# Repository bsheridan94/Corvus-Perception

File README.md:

# Corvus-Perception
IoT Data Fusion Engine for
Interior Home Application

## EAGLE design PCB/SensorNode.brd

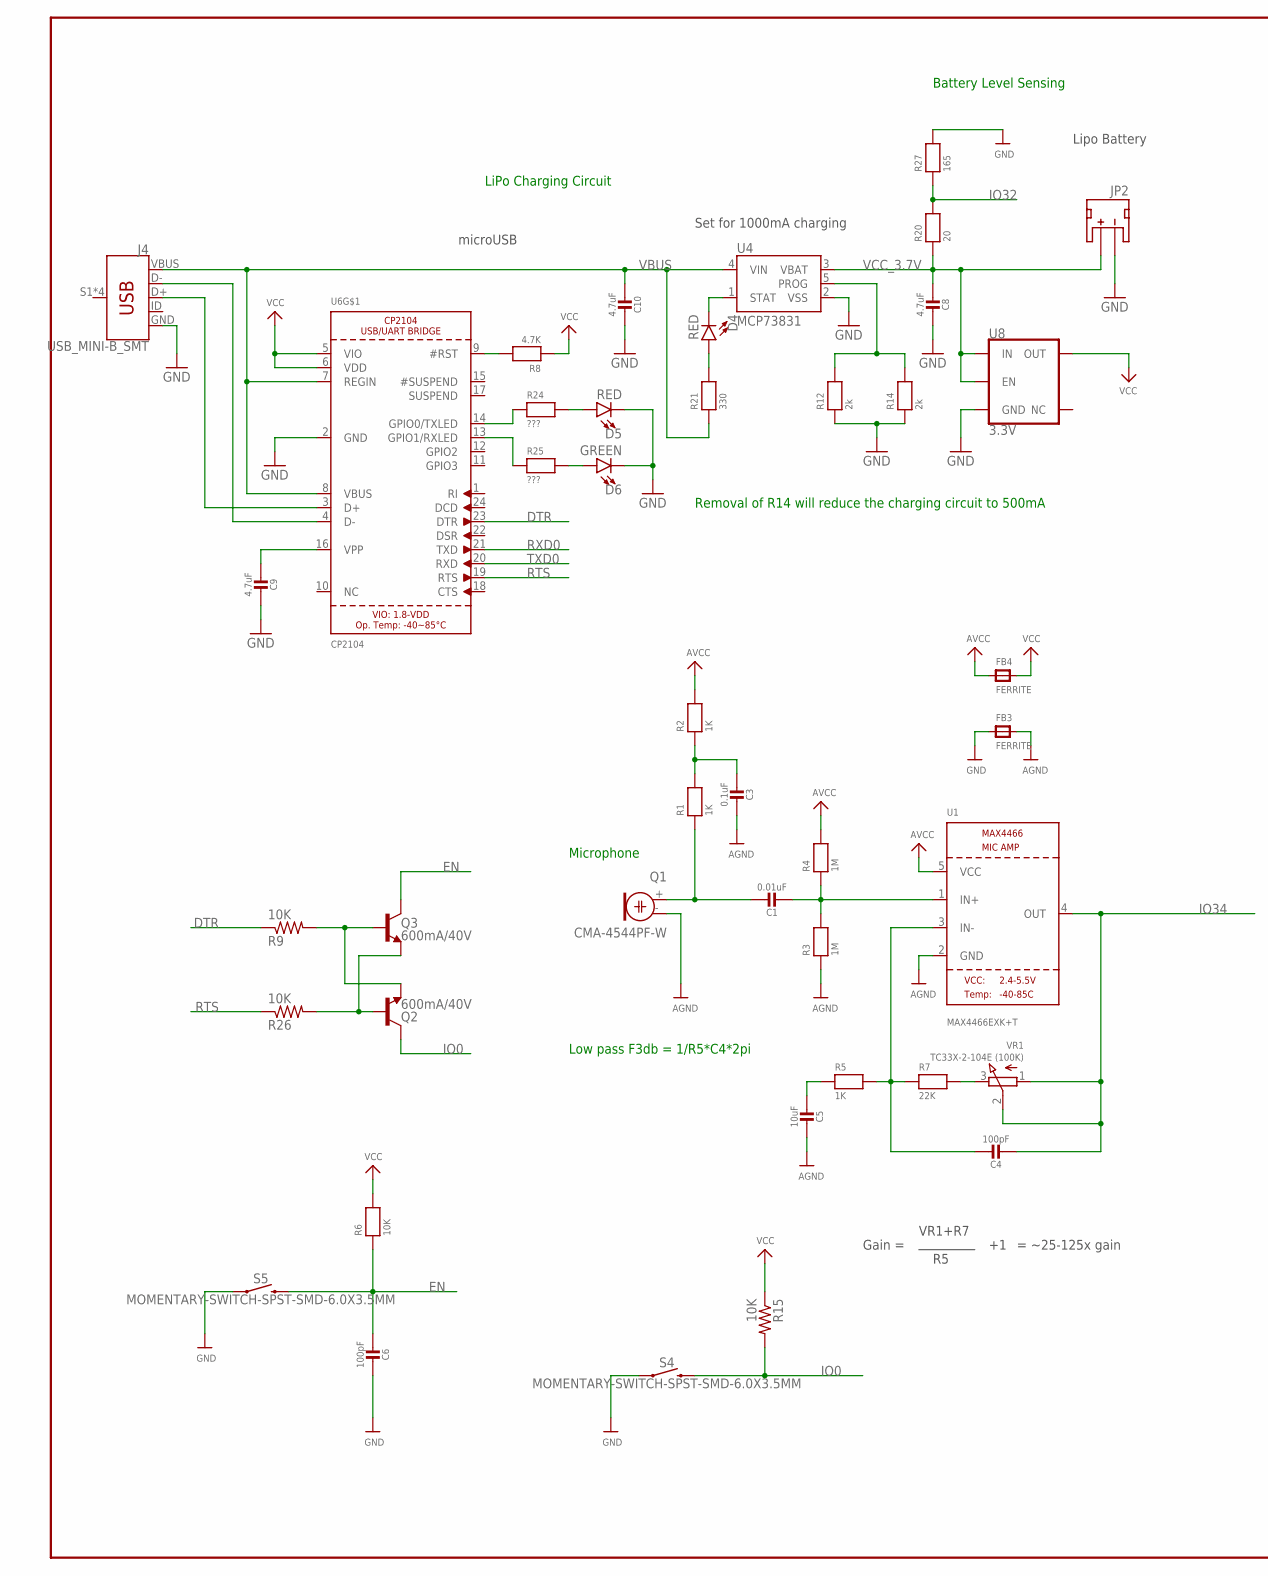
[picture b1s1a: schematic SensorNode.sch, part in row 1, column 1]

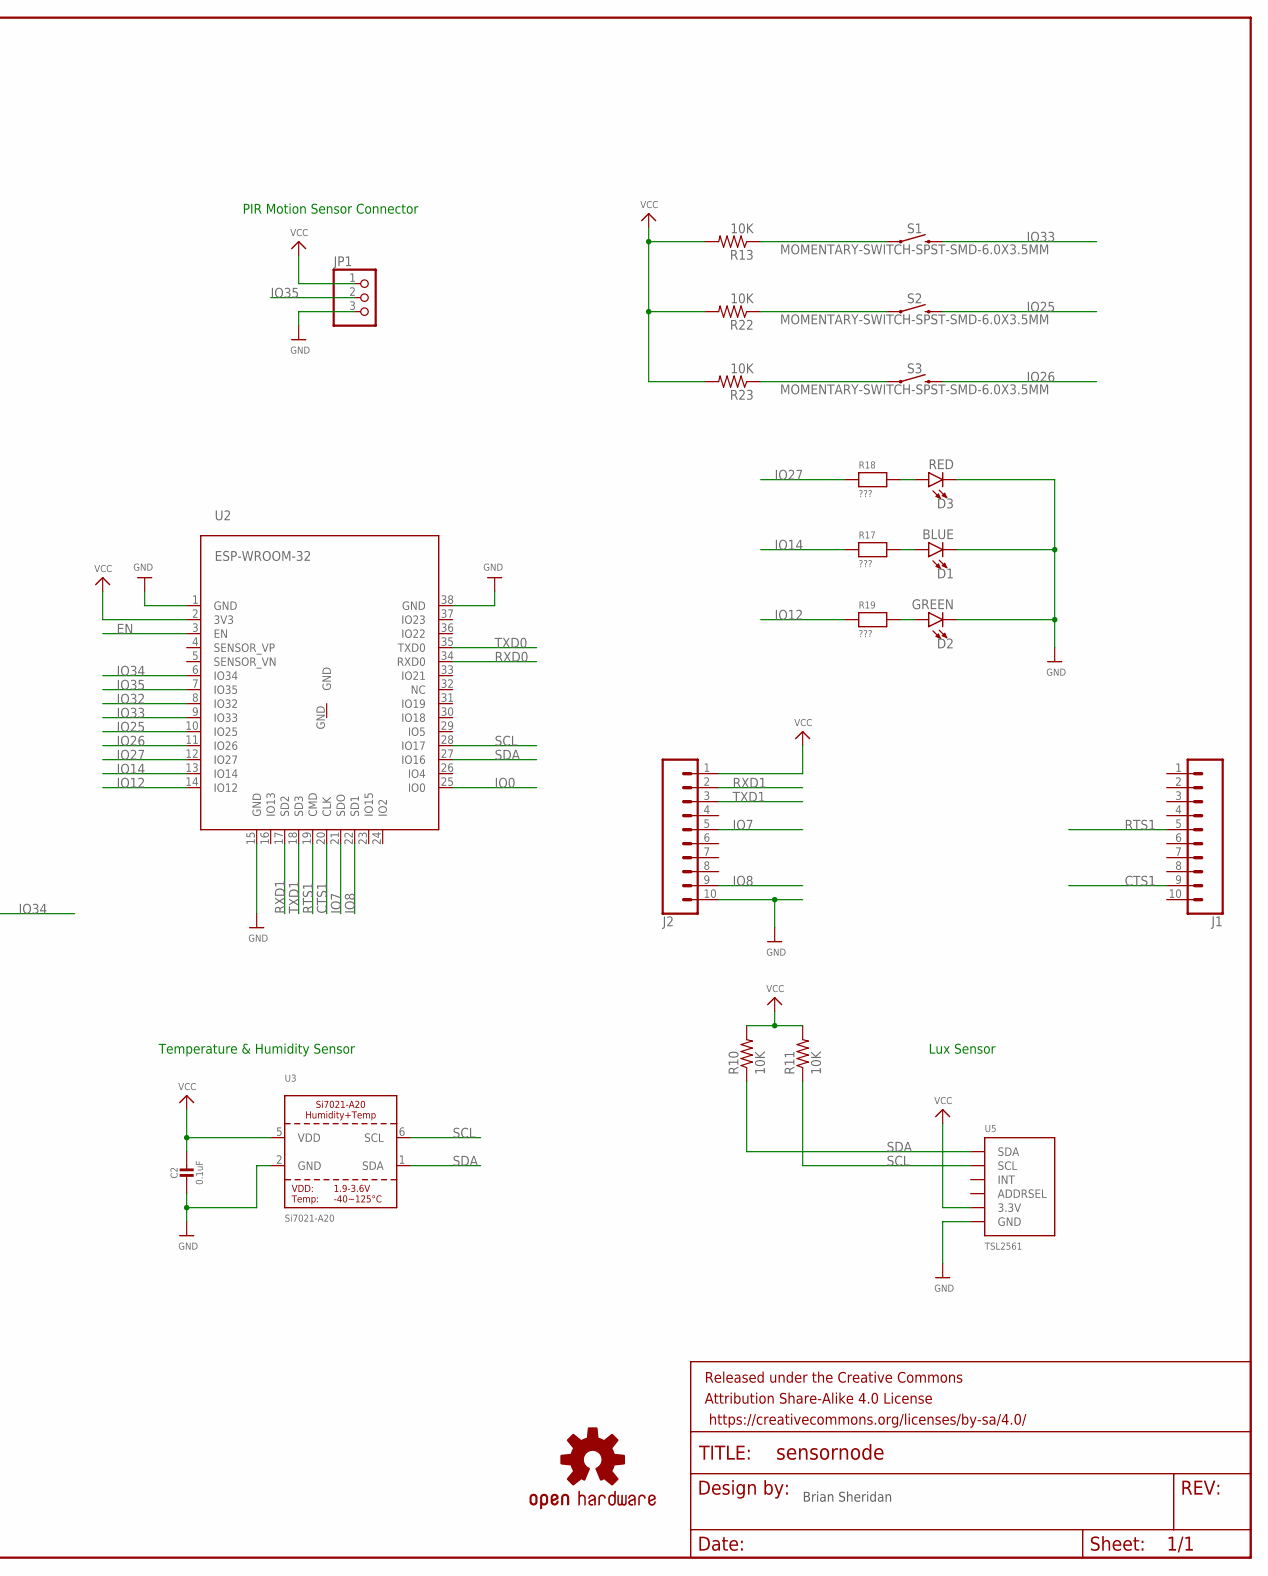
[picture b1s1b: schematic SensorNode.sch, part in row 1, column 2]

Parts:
C1: 0.01uF; 0805-NO
C2, C3: 0.1uF; 0805-NO
C4, C6: 100pF; 0805-NO
C5: 10uF; 0805-NO
C8, C9, C10: 4.7uF; 0805-NO
D1: BLUE; LED-1206
D2, D6: GREEN; LED-1206
D3, D4, D5: RED; LED-1206
FB3, FB4: FERRITE; 0805
FRAME1: FRAME-LEDGER; CREATIVE_COMMONS
J1, J2: CONN_102MMSMD; 1X10-2MM-SMD
J4: USB_MINI-B_SMT; USB-MINIB
JP1: HEADER-1X376MIL; 1X03_ROUND_76
JP2: JST; JST-2-SMD
LOGO1: OSHW-LOGOM; OSHW-LOGO-M
Q1: CMA-4544PF-W; ELECTRET_9.7
Q2, Q3: 600mA/40V; SOT23-3
R1, R2, R5: 1K; 0805
R3, R4: 1M; 0805
R6: 10K; 0805
R7: 22K; 0805
R8: 4.7K; 0805
R9, R10, R11, R13, R15, R22, R23, R26: 10K; R0805
R12, R14: 2k; 0805
R17, R18, R19, R24, R25: ???; 0805
R20: 20; 0805
R21: 330; 0805
R27: 165; 0805
S1, S2, S3, S4, S5: MOMENTARY-SWITCH-SPST-SMD-6.0X3.5MM; TACTILE_SWITCH_SMD_6.0X3.5MM
U1: MAX4466EXK+T; SC70-5
U2: ESP-WROOM-32
U3: Si7021-A20; DFN6_3X3_SI
U4: MCP73831; SOT23-5
U5: TSL2561; TSL2561_FN
U6: CP2104; QFN24_4MM_SMSC
U8: 3.3V; SOT23-5
VR1: TC33X-2-104E (100K); TRIMPOT_BOURNS_TC33X-2

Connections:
AGND: C3.1, C5.1, FB3.2, Q1.- (1), R3.1, U1.2 (GND)
AVCC: FB4.1, R2.2, R4.2, U1.5 (VCC)
CTS1: J1.9, U2.20 (CLK)
DTR: R9.1, U6.23 (DTR)
EN: C6.2, Q3.3 (C), R6.1, S5.2, U2.3 (EN)
GND: C2.2, C6.1, C8.1, C9.1, C10.1, D1.C, D2.C, D3.C, D5.C, D6.C, FB3.1, J2.10, J4.GND, JP1.3, JP2.1 (-), R12.1, R14.1, R27.2, S4.1, S5.1, U2.1 (GND), U2.15 (GND), U2.38 (GND), U3.2 (GND), U4.2 (VSS), U5.VSS (GND), U6.2 (GND), U8.2 (GND)
IO0: Q2.3 (C), R15.2, S4.2, U2.25 (IO0)
IO7: J2.5, U2.21 (SDO)
IO8: J2.9, U2.22 (SD1)
IO12: R19.1, U2.14 (IO12)
IO14: R17.1, U2.13 (IO14)
IO25: S2.2, U2.10 (IO25)
IO26: S3.2, U2.11 (IO26)
IO27: R18.1, U2.12 (IO27)
IO32: R20.2, R27.1, U2.8 (IO32)
IO33: S1.2, U2.9 (IO33)
IO34: C4.2, U1.4 (OUT), U2.6 (IO34), VR1.1 (A), VR1.2 (S)
IO35: JP1.2, U2.7 (IO35)
unnamed: C1.1, Q1.+ (2), R1.1
unnamed: C1.2, R3.2, R4.1, U1.1 (IN+)
unnamed: C4.1, R5.2, R7.1, U1.3 (IN-)
unnamed: C5.2, R5.1
unnamed: R7.2, VR1.3 (E)
unnamed: C9.2, U6.16 (VPP)
unnamed: R8.2, U6.9 (#RST)
unnamed: Q2.2 (E), Q3.1 (B), R9.2
unnamed: Q2.1 (B), Q3.2 (E), R26.2
unnamed: D4.A, R21.2
unnamed: R13.1, S1.1
unnamed: D3.A, R18.2
unnamed: D1.A, R17.2
unnamed: D2.A, R19.2
unnamed: R22.1, S2.1
unnamed: R23.1, S3.1
unnamed: C3.2, R1.2, R2.1
unnamed: J4.D-, U6.4 (D-)
unnamed: J4.D+, U6.3 (D+)
unnamed: D5.A, R24.2
unnamed: R24.1, U6.14 (GPIO0/TXLED)
unnamed: R25.1, U6.13 (GPIO1/RXLED)
unnamed: D6.A, R25.2
PROG: R12.2, R14.2, U4.5 (PROG)
RTS: R26.1, U6.19 (RTS)
RTS1: J1.5, U2.19 (CMD)
RXD0: U2.34 (RXD0), U6.21 (TXD)
RXD1: J2.2, U2.17 (SD2)
SCL: R11.1, U2.28 (IO17), U3.6 (SCL), U5.CLK (SCL)
SDA: R10.1, U2.27 (IO16), U3.1 (SDA), U5.DATA (SDA)
STAT: D4.C, U4.1 (STAT)
TP: U6.THERM (TP)
TXD0: U2.35 (TXD0), U6.20 (RXD)
TXD1: J2.3, U2.18 (SD3)
VBUS: C10.2, J4.VBUS, R21.1, U4.4 (VIN), U6.7 (REGIN), U6.8 (VBUS)
VCC: C2.1, FB4.2, J2.1, JP1.1, R6.2, R8.1, R10.2, R11.2, R13.2, R15.1, R22.2, R23.2, U2.2 (3V3), U3.5 (VDD), U5.VDD (3.3V), U6.5 (VIO), U6.6 (VDD), U8.5 (OUT)
VCC_3.7V: C8.2, JP2.2 (+), R20.1, U4.3 (VBAT), U8.1 (IN), U8.3 (EN)

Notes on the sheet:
Gain =
VR1+R7
= ~25-125x gain
Low pass F3db = 1/R5*C4*2pi
PIR Motion Sensor Connector
Set for 1000mA charging
microUSB
Lipo Battery
LiPo Charging Circuit
Microphone
Temperature & Humidity Sensor
Lux Sensor
Battery Level Sensing
Removal of R14 will reduce the charging circuit to 500mA
Brian Sheridan

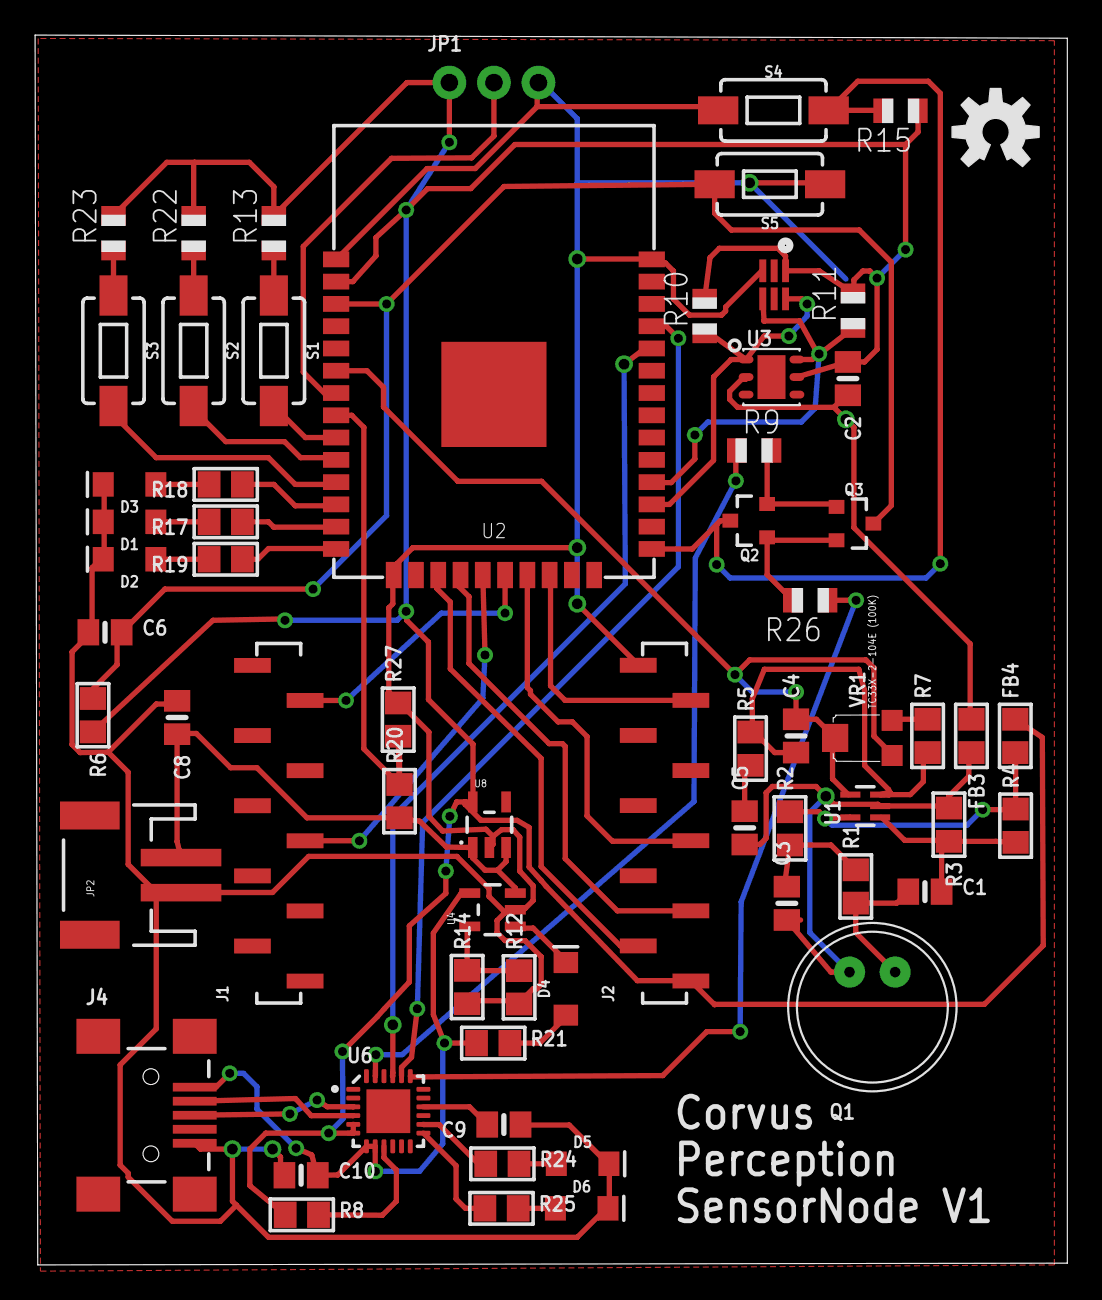
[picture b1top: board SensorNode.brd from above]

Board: 2 copper layers, 58.9 x 70.1 mm, 66 parts (0 on the bottom side), 54 nets.

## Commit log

2017-02-05 :tada: Added .gitattributes & .gitignore files
2017-02-05 Inital Commit. Migration from STM32F4 to ESP32
2017-02-05 Added hardware Documentation
2017-02-07 PCB Improvements, layout planned out
    Moved components around on layout to minimize pcb space. Battery moved
    to back of board. Minor schematic improvements. ESP32 template added
2017-02-08 Added USB to UART and Auto Reset Circuit
2017-02-23 Reset and Bootloader PushButtons, Replaced USB
    USB micro to mini due to supply issues.
    SMD Xbee headers
    New voltage regulator
2017-02-26 Created Android Wear App
    Sets the smart watch's bluetooth to discoverable.
2017-02-27 Add files via upload
    Website Template
2017-02-28 Fixed Net Issues, Started Routing
2017-03-01 Mid Route Check Point
2017-03-02 Commit Before AutoRouting
2017-03-02 Fully Routed
2017-03-02 Added system health icon
2017-03-10 Post DRC layout
2017-03-11 Added demo script and template updates
    Fixed acknowledgement button
    Added slider to webpage (not active)
    Added demo php file
2017-03-12 Rewrote Awknowledgement Button
    Added working acknowledgement for each alert
    Connected MySQL database to web front end
2017-03-13 Temperature Alert Working
    Added "test/debug" panel
    Fixed Acknowledgement button to be more accurate
    Added temperature test case
2017-05-03 Added Working Sensitivity Functions
2017-05-06 testing ts12561
2017-05-13 Working TSL2561 Driver
2017-05-22 Added Alexa Support
2017-05-22 fall detection
2017-05-22 fall
2017-05-25 Fall Alert
    Python code for Pi when user falls
2017-05-25 Updated to remove logger error
2017-05-25 Added dynamic temperature Alert
2017-05-25 Pi to AWS RDS script
    Once the packet is parsed, this adds all the data to the appropriate table
2017-05-26 Fall alerts for both Alexa & Lex Lambda Functions
2017-05-26 Updated website for presentation

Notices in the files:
parts and their libraries:
microbuilder: This work is placed in the public domain, and may be freely used for commercial and non-commercial work with the following conditions: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
SparkFun-Connectors: Licensing: Creative Commons ShareAlike 4.0 International - https://creativecommons.org/licenses/by-sa/4.0
